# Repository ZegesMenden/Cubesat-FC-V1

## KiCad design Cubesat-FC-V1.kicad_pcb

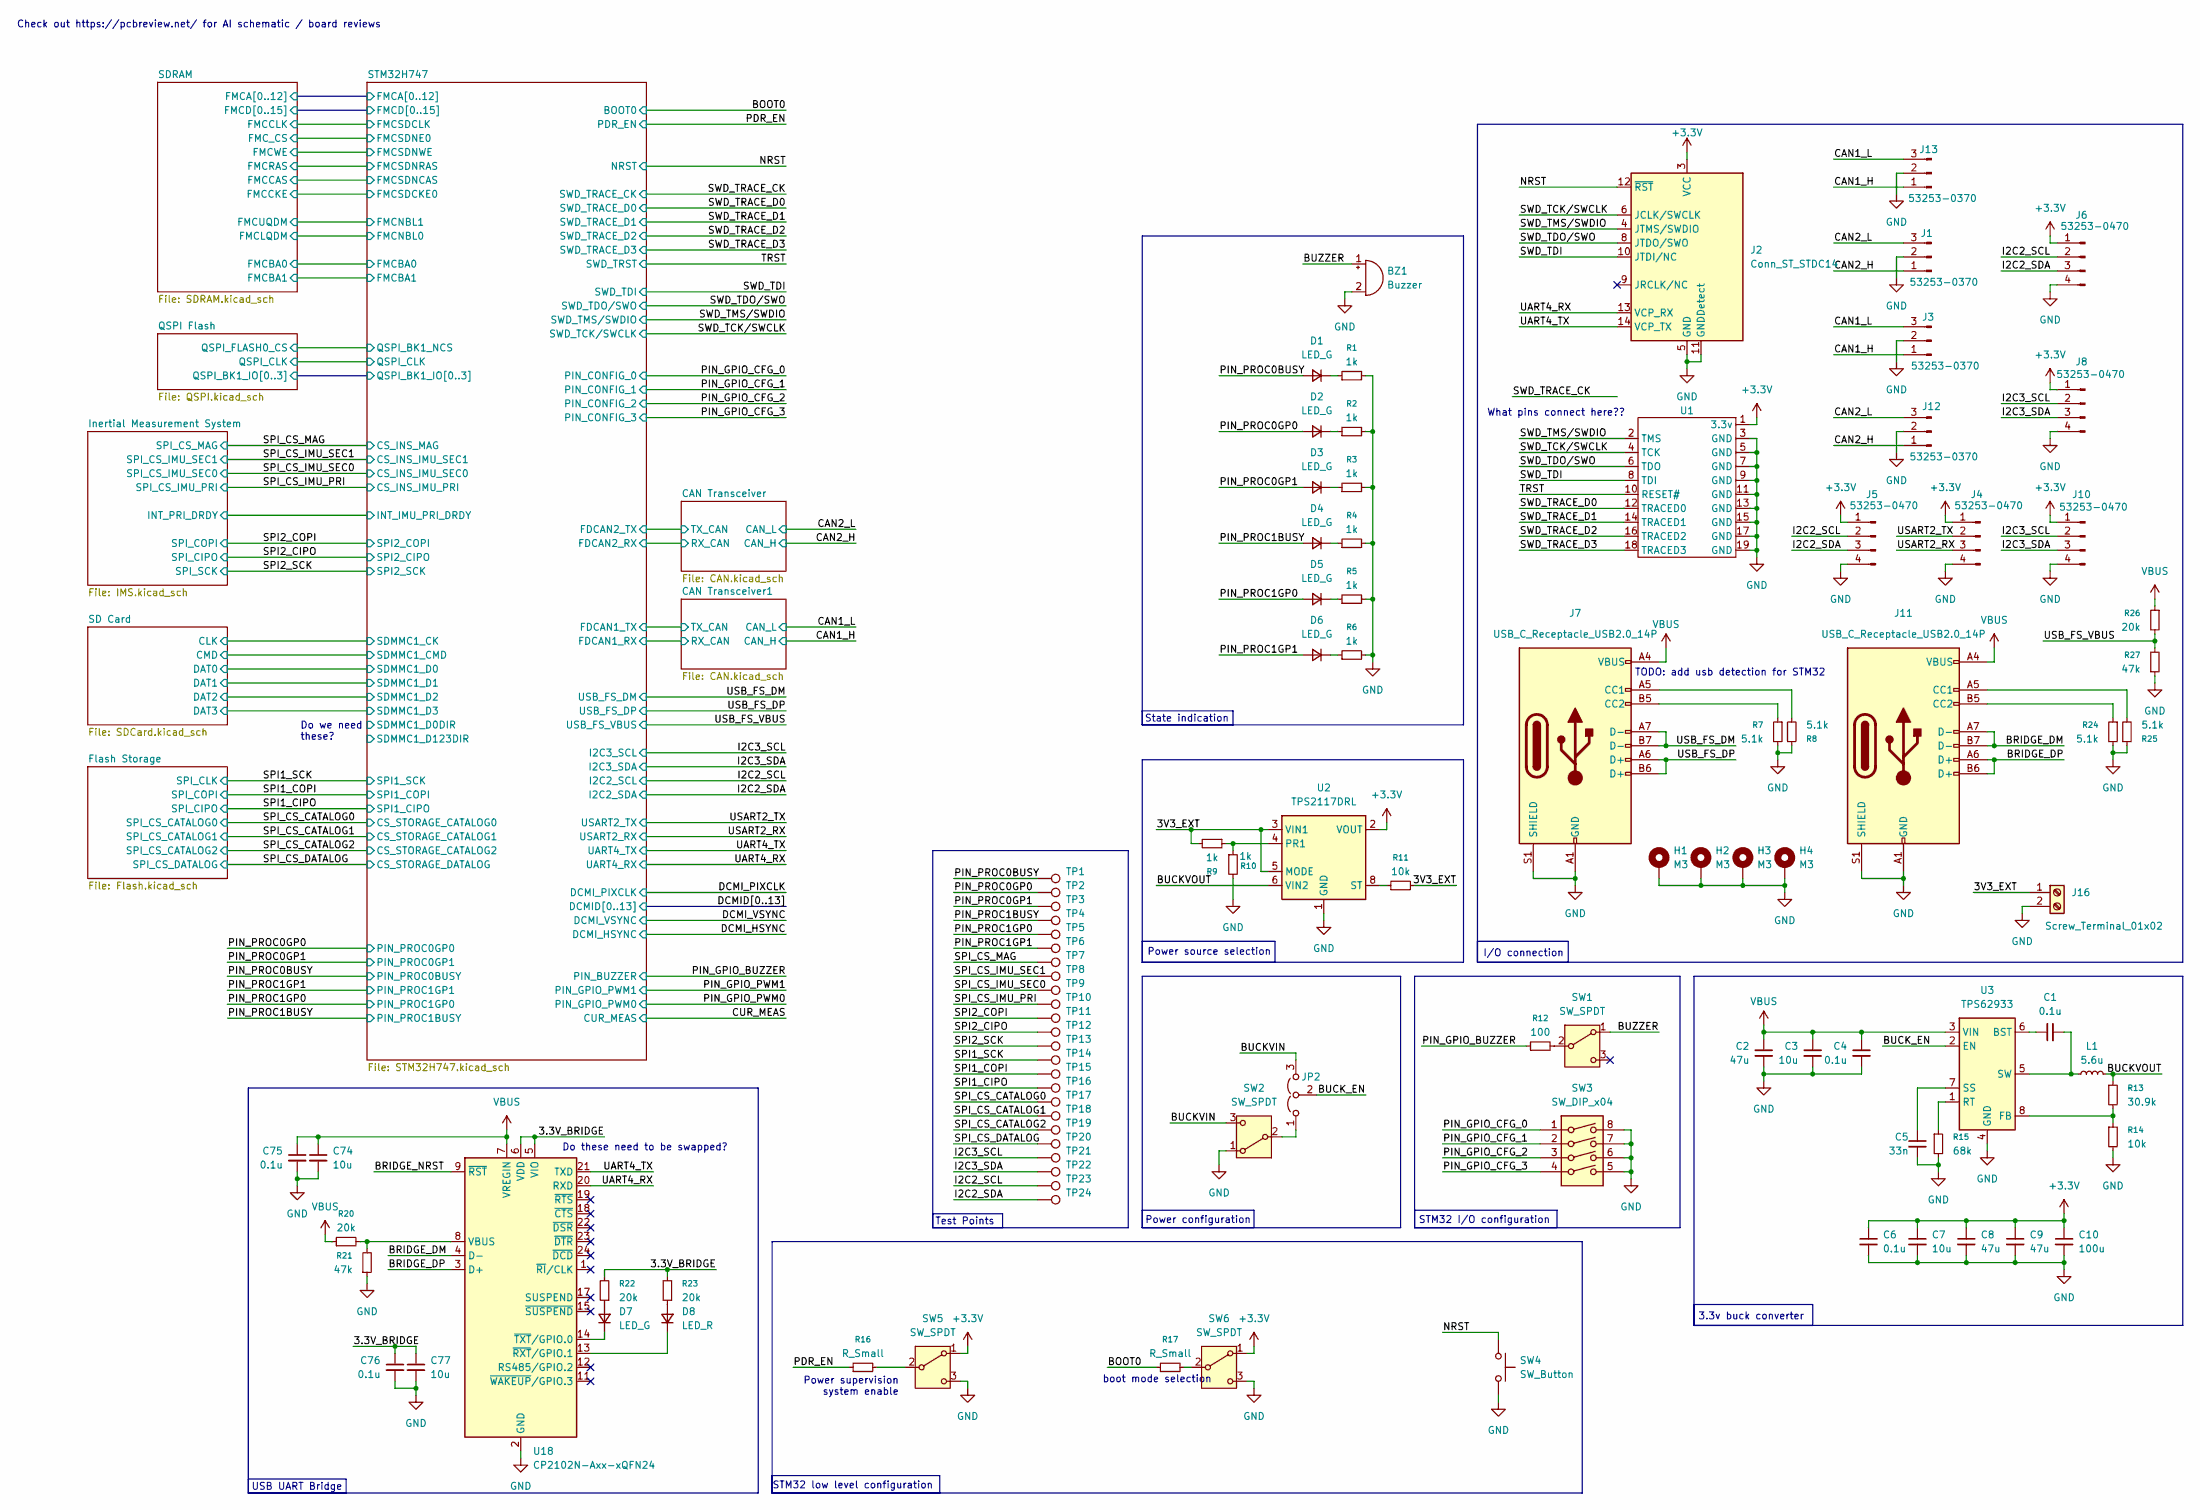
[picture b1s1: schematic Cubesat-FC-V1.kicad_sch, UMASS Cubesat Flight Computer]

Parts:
BZ1: Buzzer; Buzzer_Murata_PKMCS0909E
C1, C75, C76: 0.1u; C_0402_1005Metric; voltage 10
C2, C8, C9: 47u; C_1206_3216Metric; voltage 30
C3, C7: 10u; C_1206_3216Metric; voltage 30
C4, C6: 0.1u; C_1206_3216Metric; voltage 30
C5: 33n; C_0402_1005Metric; voltage 10
C10: 100u; C_1206_3216Metric; voltage 30
C74, C77: 10u; C_0402_1005Metric; voltage 10
D1, D2, D3, D4, D5, D6, D7: LED_G; LED_0603_1608Metric
D8: LED_R; LED_0603_1608Metric
H1, H2, H3, H4: M3; MountingHole_3.2mm_M3_ISO7380_Pad_TopBottom
J1, J3, J12, J13: 53253-0370; Molex_Micro-Latch_53253-0370_1x03_P2.00mm_Vertical
J2: Conn_ST_STDC14; PinHeader_2x07_P2.54mm_Vertical
J4, J5, J6, J8, J10: 53253-0470; Molex_Micro-Latch_53253-0470_1x04_P2.00mm_Vertical
J7, J11: USB_C_Receptacle_USB2.0_14P; USB_C_Receptacle_GCT_USB4105-xx-A_16P_TopMnt_Horizontal
J16: Screw_Terminal_01x02; TerminalBlock_Phoenix_MKDS-1,5-2-5.08_1x02_P5.08mm_Horizont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
JP2: Jumper_3_Open; SolderJumper-3_P1.3mm_Open_RoundedPad1.0x1.5mm
L1: 5.6u; L_Coilcraft_XAL7070-XXX
R1, R2, R3, R4, R5, R6, R9, R10: 1k; R_0402_1005Metric; voltage 50
R7, R8, R24, R25: 5.1k; R_0402_1005Metric; voltage 50
R11, R14: 10k; R_0402_1005Metric; voltage 50
R12: 100; R_0402_1005Metric; voltage 50
R13: 30.9k; R_0402_1005Metric; voltage 50
R15: 68k; R_0402_1005Metric; voltage 50
R16, R17: R_Small; R_0402_1005Metric; voltage 50
R20, R22, R23, R26: 20k; R_0402_1005Metric; voltage 50
R21, R27: 47k; R_0402_1005Metric; voltage 50
SW1, SW2, SW5, SW6: SW_SPDT; SW_CK_JS202011CQN_DPDT_Straight
SW3: SW_DIP_x04; SW_DIP_SPSTx04_Slide_6.7x11.72mm_W7.62mm_P2.54mm_LowProfile
SW4: SW_Button; SW_SPST_PTS810
TP1, TP2, TP3, TP4, TP5, TP6, TP7, TP8, TP9, TP10, TP11, TP12, TP13, TP14, TP15, TP16, TP17, TP18, TP19, TP20, TP21, TP22, TP23, TP24: TestPoint; TestPoint_Pad_D1.5mm
U1: PinHeader_2x10_P2.54mm_Vertical
U2: TPS2117DRL; SOT-583-8
U3: TPS62933; SOT-583-8
U18: CP2102N-Axx-xQFN24; QFN-24-1EP_4x4mm_P0.5mm_EP2.6x2.6mm

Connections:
+3.3V: C6.1, C7.1, C8.1, C9.1, C10.1, J2.3 (VCC), J4.1, J5.1, J6.1, J8.1, J10.1, SW5.1 (A), SW6.1 (A), U1.1 (3.3v), U2.2 (VOUT), U2.7 (VOUT); also elsewhere on the board
/3.3V_BRIDGE: C76.1, C77.1, R22.2, R23.2, U18.5 (VIO), U18.6 (VDD)
/3V3_EXT: J16.1, R9.2, R11.2, U2.3 (VIN1), U2.5 (MODE)
/BOOT0: R17.1; also elsewhere on the board
/BRIDGE_DM: J11.A7 (D-), J11.B7 (D-), U18.4 (D-)
/BRIDGE_DP: J11.A6 (D+), J11.B6 (D+), U18.3 (D+)
/BRIDGE_NRST: U18.9 (~RST)
/BUCKVIN: JP2.3 (B), SW2.3 (C)
/BUCKVOUT: L1.2, R13.1, U2.6 (VIN2)
/BUCK_EN: JP2.2 (C), U3.2 (EN)
/BUZZER: BZ1.1 (+), SW1.1 (A)
/CAN1_H: J3.1, J13.1; also elsewhere on the board
/CAN1_L: J3.3, J13.3; also elsewhere on the board
/CAN2_H: J1.1, J12.1; also elsewhere on the board
/CAN2_L: J1.3, J12.3; also elsewhere on the board
/I2C2_SCL: J5.2, J6.2, TP23.1; also elsewhere on the board
/I2C2_SDA: J5.3, J6.3, TP24.1; also elsewhere on the board
/I2C3_SCL: J8.2, J10.2, TP21.1; also elsewhere on the board
/I2C3_SDA: J8.3, J10.3, TP22.1; also elsewhere on the board
/NRST: J2.12 (~RST), SW4.1; also elsewhere on the board
/PDR_EN: R16.1; also elsewhere on the board
/PIN_GPIO_BUZZER: R12.1; also elsewhere on the board
/PIN_GPIO_CFG_0: SW3.1; also elsewhere on the board
/PIN_GPIO_CFG_1: SW3.2; also elsewhere on the board
/PIN_GPIO_CFG_2: SW3.3; also elsewhere on the board
/PIN_GPIO_CFG_3: SW3.4; also elsewhere on the board
/PIN_PROC0BUSY: D1.2 (A), TP1.1; also elsewhere on the board
/PIN_PROC0GP0: D2.2 (A), TP2.1; also elsewhere on the board
/PIN_PROC0GP1: D3.2 (A), TP3.1; also elsewhere on the board
/PIN_PROC1BUSY: D4.2 (A), TP4.1; also elsewhere on the board
/PIN_PROC1GP0: D5.2 (A), TP5.1; also elsewhere on the board
/PIN_PROC1GP1: D6.2 (A), TP6.1; also elsewhere on the board
/SPI1_CIPO: TP16.1; also elsewhere on the board
/SPI1_COPI: TP15.1; also elsewhere on the board
/SPI1_SCK: TP14.1; also elsewhere on the board
/SPI2_CIPO: TP12.1; also elsewhere on the board
/SPI2_COPI: TP11.1; also elsewhere on the board
/SPI2_SCK: TP13.1; also elsewhere on the board
/SPI_CS_CATALOG0: TP17.1; also elsewhere on the board
/SPI_CS_CATALOG1: TP18.1; also elsewhere on the board
/SPI_CS_CATALOG2: TP19.1; also elsewhere on the board
/SPI_CS_DATALOG: TP20.1; also elsewhere on the board
/SPI_CS_IMU_PRI: TP10.1; also elsewhere on the board
/SPI_CS_IMU_SEC0: TP9.1; also elsewhere on the board
/SPI_CS_IMU_SEC1: TP8.1; also elsewhere on the board
/SPI_CS_MAG: TP7.1; also elsewhere on the board
/SWD_TCK/SWCLK: J2.6 (JCLK/SWCLK), U1.4 (TCK); also elsewhere on the board
/SWD_TDI: J2.10 (JTDI/NC), U1.8 (TDI); also elsewhere on the board
/SWD_TDO/SWO: J2.8 (JTDO/SWO), U1.6 (TDO); also elsewhere on the board
/SWD_TMS/SWDIO: J2.4 (JTMS/SWDIO), U1.2 (TMS); also elsewhere on the board
/SWD_TRACE_D0: U1.12 (TRACED0); also elsewhere on the board
/SWD_TRACE_D1: U1.14 (TRACED1); also elsewhere on the board
/SWD_TRACE_D2: U1.16 (TRACED2); also elsewhere on the board
/SWD_TRACE_D3: U1.18 (TRACED3); also elsewhere on the board
/TRST: U1.10 (RESET#); also elsewhere on the board
/UART4_RX: J2.13 (VCP_RX), U18.20 (RXD); also elsewhere on the board
/UART4_TX: J2.14 (VCP_TX), U18.21 (TXD); also elsewhere on the board
/USART2_RX: J4.3; also elsewhere on the board
/USART2_TX: J4.2; also elsewhere on the board
/USB_FS_DM: J7.A7 (D-), J7.B7 (D-); also elsewhere on the board
/USB_FS_DP: J7.A6 (D+), J7.B6 (D+); also elsewhere on the board
/USB_FS_VBUS: R26.2, R27.2; also elsewhere on the board
GND: BZ1.2 (-), C2.2, C3.2, C4.2, C5.2, C6.2, C7.2, C8.2, C9.2, C10.2, C74.2, C75.2, C76.2, C77.2, H1.1, H2.1, H3.1, H4.1, J1.2, J2.5 (GND), J2.7 (GND), J2.11 (GNDDetect), J3.2, J4.4, J5.4, J6.4, J7.A1 (GND), J7.A12 (GND), J7.B1 (GND), J7.B12 (GND), J7.S1 (SHIELD), J8.4, J10.4, J11.A1 (GND), J11.A12 (GND), J11.B1 (GND), J11.B12 (GND), J11.S1 (SHIELD), J12.2, J13.2, J16.2, R1.2, R2.2, R3.2, R4.2, R5.2, R6.2, R7.2, R8.1, R10.2, R14.2, R15.2, R21.1, R24.2, R25.1, R27.1, SW2.1 (A), SW3.5, SW3.6, SW3.7, SW3.8, SW4.2, SW5.3 (C), SW6.3 (C), U1.3 (GND), U1.5 (GND), U1.7 (GND), U1.9 (GND), U1.11 (GND), U1.13 (GND), U1.15 (GND), U1.17 (GND), U1.19 (GND), U2.1 (GND), U3.4 (GND), U18.2 (GND), U18.25 (GND); also elsewhere on the board
unnamed: D1.1 (K), R1.1
unnamed: D2.1 (K), R2.1
unnamed: D3.1 (K), R3.1
unnamed: D4.1 (K), R4.1
unnamed: D5.1 (K), R5.1
unnamed: D6.1 (K), R6.1
unnamed: D7.2 (A), R22.1
unnamed: D7.1 (K), U18.14 (~TXT/GPIO.0)
unnamed: D8.2 (A), R23.1
unnamed: D8.1 (K), U18.13 (~RXT/GPIO.1)
unnamed: J7.A5 (CC1), R8.2
unnamed: J7.B5 (CC2), R7.1
unnamed: J11.A5 (CC1), R25.2
unnamed: J11.B5 (CC2), R24.1
unnamed: JP2.1 (A), SW2.2 (B)
unnamed: R12.2, SW1.2 (B)
unnamed: R16.2, SW5.2 (B)
unnamed: R17.2, SW6.2 (B)
unnamed: R9.1, R10.1, U2.4 (PR1)
unnamed: R11.1, U2.8 (ST)
unnamed: C1.1, U3.6 (BST)
unnamed: R13.2, R14.1, U3.8 (FB)
unnamed: R15.1, U3.1 (RT)
unnamed: C5.1, U3.7 (SS)
unnamed: C1.2, L1.1, U3.5 (SW)
unnamed: R20.2, R21.2, U18.8 (VBUS)
VBUS: C2.1, C3.1, C4.1, C74.1, C75.1, J7.A4 (VBUS), J7.A9 (VBUS), J7.B4 (VBUS), J7.B9 (VBUS), J11.A4 (VBUS), J11.A9 (VBUS), J11.B4 (VBUS), J11.B9 (VBUS), R20.1, R26.1, U3.3 (VIN), U18.7 (VREGIN)

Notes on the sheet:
Test Points
Power configuration
Do these need to be swapped?
I/O connection
Power source selection
TODO: add usb detection for STM32
Do we need these?
boot mode selection
Check out https://pcbreview.net/ for AI schematic / board reviews
USB UART Bridge
3.3v buck converter
STM32 low level configuration
What pins connect here??
STM32 I/O configuration
State indication
Power supervision system enable

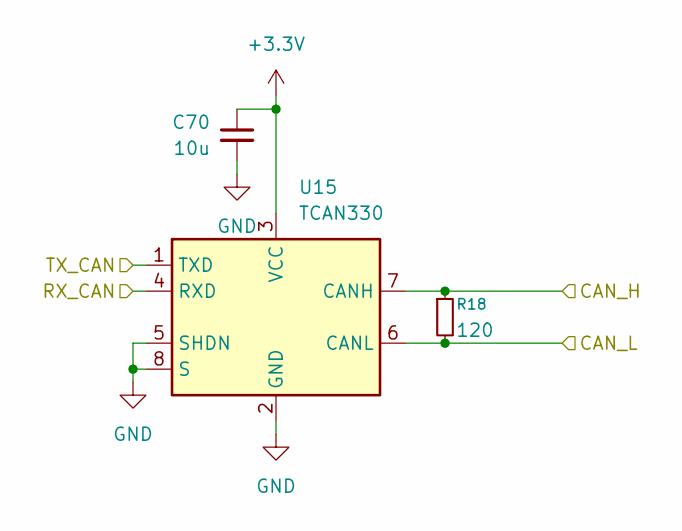
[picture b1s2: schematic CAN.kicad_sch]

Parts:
C70: 10u; C_0402_1005Metric; voltage 5
R18: 120; R_0402_1005Metric; voltage 5
U15: TCAN330; SOT-23-8

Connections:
+3.3V: C70.1, U15.3 (VCC); also elsewhere on the board
/CAN2_H: R18.1, U15.7 (CANH); also elsewhere on the board
/CAN2_L: R18.2, U15.6 (CANL); also elsewhere on the board
/CAN Transceiver/RX_CAN: U15.4 (RXD); also elsewhere on the board
/CAN Transceiver/TX_CAN: U15.1 (TXD); also elsewhere on the board
GND: C70.2, U15.2 (GND), U15.5 (SHDN), U15.8 (S); also elsewhere on the board

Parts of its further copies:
C72: 10u; C_0402_1005Metric; voltage 5
R19: 120; R_0402_1005Metric; voltage 5
U16: TCAN330; SOT-23-8

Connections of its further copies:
+3.3V: C72.1, U16.3 (VCC); also elsewhere on the board
/CAN1_H: R19.1, U16.7 (CANH); also elsewhere on the board
/CAN1_L: R19.2, U16.6 (CANL); also elsewhere on the board
/CAN Transceiver1/RX_CAN: U16.4 (RXD); also elsewhere on the board
/CAN Transceiver1/TX_CAN: U16.1 (TXD); also elsewhere on the board
GND: C72.2, U16.2 (GND), U16.5 (SHDN), U16.8 (S); also elsewhere on the board

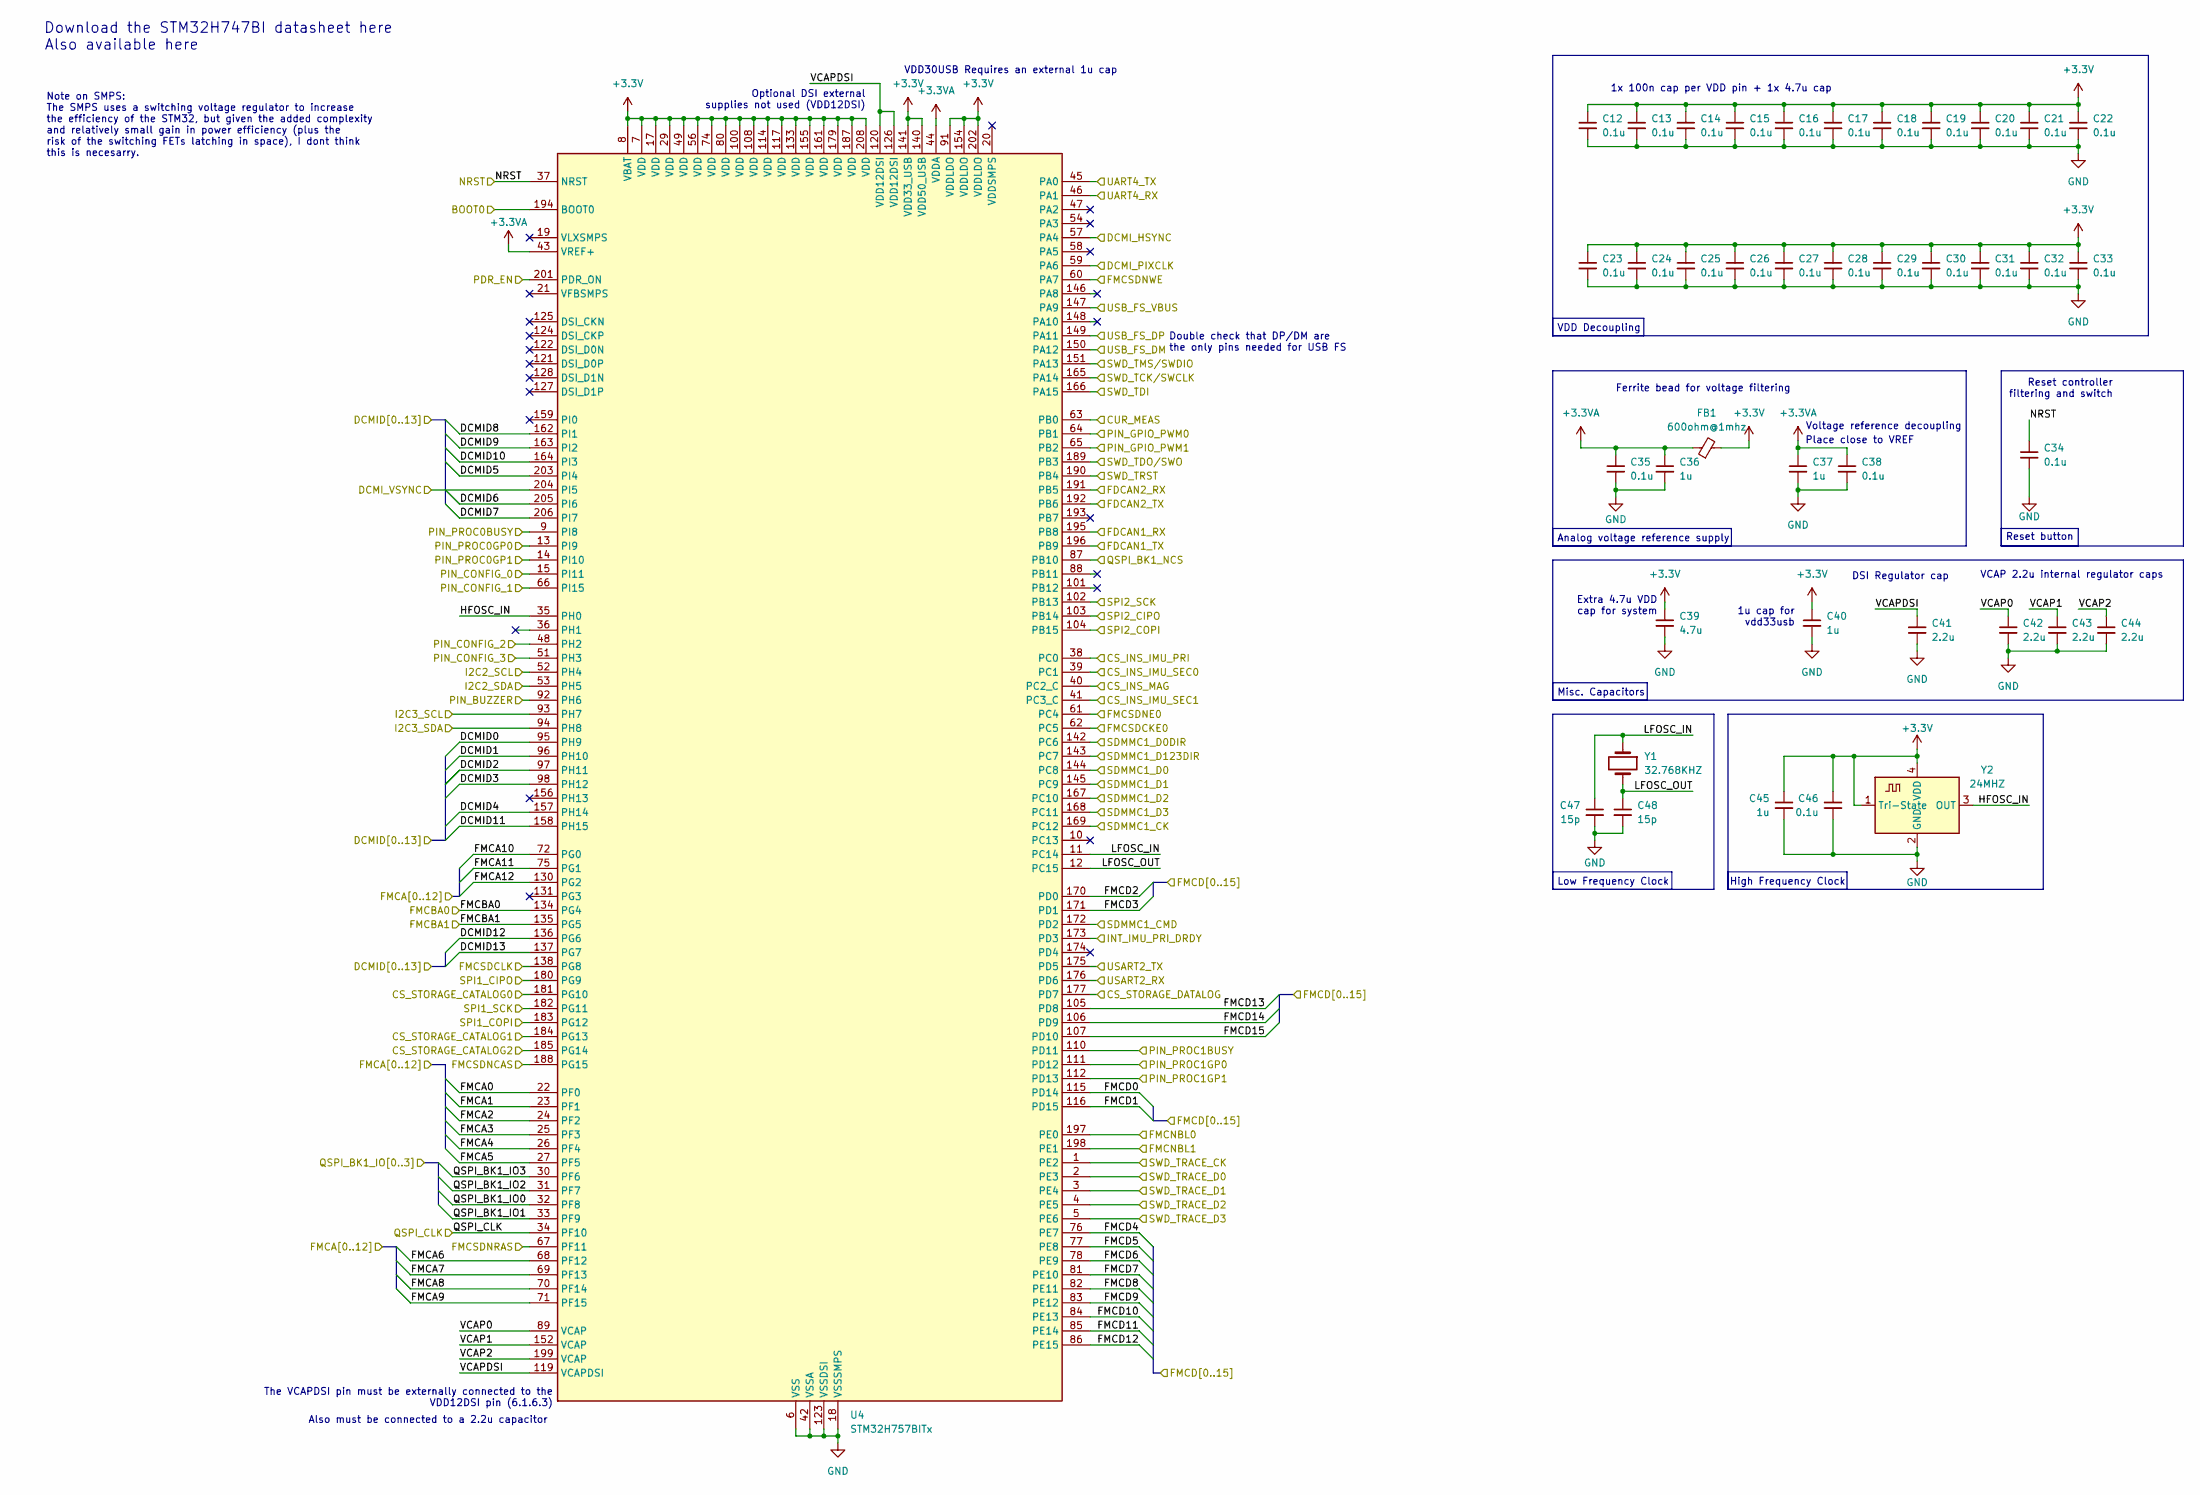
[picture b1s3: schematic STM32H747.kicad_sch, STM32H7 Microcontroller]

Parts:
C12, C13, C14, C15, C16, C17, C18, C19, C20, C21, C22, C23, C24, C25, C26, C27, C28, C29, C30, C31, C32, C33, C34, C35, C38, C46: 0.1u; C_0402_1005Metric; voltage 10
C36, C37, C40, C45: 1u; C_0402_1005Metric; voltage 10
C39: 4.7u; C_0402_1005Metric; voltage 10
C41, C42, C43, C44: 2.2u; C_0402_1005Metric; voltage 10
C47, C48: 15p; C_0402_1005Metric; voltage 10
FB1: 600ohm@1mhz; R_0402_1005Metric
U4: STM32H757BITx; LQFP-208_28x28mm_P0.5mm
Y1: 32.768KHZ; Crystal_SMD_Abracon_ABM3-2Pin_5.0x3.2mm
Y2: 24MHZ; Oscillator_SMD_Abracon_ASCO-4Pin_1.6x1.2mm

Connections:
+3.3V: C12.1, C13.1, C14.1, C15.1, C16.1, C17.1, C18.1, C19.1, C20.1, C21.1, C22.1, C23.1, C24.1, C25.1, C26.1, C27.1, C28.1, C29.1, C30.1, C31.1, C32.1, C33.1, C39.1, C40.1, C45.1, C46.1, FB1.2, U4.7 (VDD), U4.8 (VBAT), U4.17 (VDD), U4.29 (VDD), U4.49 (VDD), U4.56 (VDD), U4.74 (VDD), U4.80 (VDD), U4.91 (VDDLDO), U4.100 (VDD), U4.108 (VDD), U4.114 (VDD), U4.117 (VDD), U4.133 (VDD), U4.140 (VDD50_USB), U4.141 (VDD33_USB), U4.154 (VDDLDO), U4.155 (VDD), U4.161 (VDD), U4.179 (VDD), U4.187 (VDD), U4.202 (VDDLDO), U4.208 (VDD), Y2.1 (Tri-State), Y2.4 (VDD); also elsewhere on the board
+3.3VA: C35.1, C36.1, C37.1, C38.1, FB1.1, U4.43 (VREF+), U4.44 (VDDA)
/BOOT0: U4.194 (BOOT0); also elsewhere on the board
/CAN Transceiver1/RX_CAN: U4.195 (PB8); also elsewhere on the board
/CAN Transceiver1/TX_CAN: U4.196 (PB9); also elsewhere on the board
/CAN Transceiver/RX_CAN: U4.191 (PB5); also elsewhere on the board
/CAN Transceiver/TX_CAN: U4.192 (PB6); also elsewhere on the board
/CUR_MEAS: U4.63 (PB0)
/DCMID0: U4.95 (PH9)
/DCMID1: U4.96 (PH10)
/DCMID2: U4.97 (PH11)
/DCMID3: U4.98 (PH12)
/DCMID4: U4.157 (PH14)
/DCMID5: U4.203 (PI4)
/DCMID6: U4.205 (PI6)
/DCMID7: U4.206 (PI7)
/DCMID8: U4.162 (PI1)
/DCMID9: U4.163 (PI2)
/DCMID10: U4.164 (PI3)
/DCMID11: U4.158 (PH15)
/DCMID12: U4.136 (PG6)
/DCMID13: U4.137 (PG7)
/DCMI_HSYNC: U4.57 (PA4)
/DCMI_PIXCLK: U4.59 (PA6)
/DCMI_VSYNC: U4.204 (PI5)
/I2C2_SCL: U4.52 (PH4); also elsewhere on the board
/I2C2_SDA: U4.53 (PH5); also elsewhere on the board
/I2C3_SCL: U4.93 (PH7); also elsewhere on the board
/I2C3_SDA: U4.94 (PH8); also elsewhere on the board
/Inertial Measurement System/INT_PRI_DRDY: U4.173 (PD3); also elsewhere on the board
/NRST: C34.1, U4.37 (NRST); also elsewhere on the board
/PDR_EN: U4.201 (PDR_ON); also elsewhere on the board
/PIN_GPIO_BUZZER: U4.92 (PH6); also elsewhere on the board
/PIN_GPIO_CFG_0: U4.15 (PI11); also elsewhere on the board
/PIN_GPIO_CFG_1: U4.66 (PI15); also elsewhere on the board
/PIN_GPIO_CFG_2: U4.48 (PH2); also elsewhere on the board
/PIN_GPIO_CFG_3: U4.51 (PH3); also elsewhere on the board
/PIN_GPIO_PWM0: U4.64 (PB1)
/PIN_GPIO_PWM1: U4.65 (PB2)
/PIN_PROC0BUSY: U4.9 (PI8); also elsewhere on the board
/PIN_PROC0GP0: U4.13 (PI9); also elsewhere on the board
/PIN_PROC0GP1: U4.14 (PI10); also elsewhere on the board
/PIN_PROC1BUSY: U4.110 (PD11); also elsewhere on the board
/PIN_PROC1GP0: U4.111 (PD12); also elsewhere on the board
/PIN_PROC1GP1: U4.112 (PD13); also elsewhere on the board
/QSPI Flash/QSPI_D0: U4.32 (PF8); also elsewhere on the board
/QSPI Flash/QSPI_D1: U4.33 (PF9); also elsewhere on the board
/QSPI Flash/QSPI_D2: U4.31 (PF7); also elsewhere on the board
/QSPI Flash/QSPI_D3: U4.30 (PF6); also elsewhere on the board
/QSPI Flash/QSPI_FLASH0_CS: U4.87 (PB10); also elsewhere on the board
/SD Card/CLK: U4.169 (PC12); also elsewhere on the board
/SD Card/CMD: U4.172 (PD2); also elsewhere on the board
/SD Card/DAT0: U4.144 (PC8); also elsewhere on the board
/SD Card/DAT1: U4.145 (PC9); also elsewhere on the board
/SD Card/DAT2: U4.167 (PC10); also elsewhere on the board
/SD Card/DAT3: U4.168 (PC11); also elsewhere on the board
/SDRAM/FMCA0: U4.22 (PF0); also elsewhere on the board
/SDRAM/FMCA1: U4.23 (PF1); also elsewhere on the board
/SDRAM/FMCA2: U4.24 (PF2); also elsewhere on the board
/SDRAM/FMCA3: U4.25 (PF3); also elsewhere on the board
/SDRAM/FMCA4: U4.26 (PF4); also elsewhere on the board
/SDRAM/FMCA5: U4.27 (PF5); also elsewhere on the board
/SDRAM/FMCA6: U4.68 (PF12); also elsewhere on the board
/SDRAM/FMCA7: U4.69 (PF13); also elsewhere on the board
/SDRAM/FMCA8: U4.70 (PF14); also elsewhere on the board
/SDRAM/FMCA9: U4.71 (PF15); also elsewhere on the board
/SDRAM/FMCA10: U4.72 (PG0); also elsewhere on the board
/SDRAM/FMCA11: U4.75 (PG1); also elsewhere on the board
/SDRAM/FMCA12: U4.130 (PG2); also elsewhere on the board
/SDRAM/FMCCAS: U4.188 (PG15); also elsewhere on the board
/SDRAM/FMCCKE: U4.62 (PC5); also elsewhere on the board
/SDRAM/FMCCLK: U4.138 (PG8); also elsewhere on the board
/SDRAM/FMCD0: U4.115 (PD14); also elsewhere on the board
/SDRAM/FMCD1: U4.116 (PD15); also elsewhere on the board
/SDRAM/FMCD2: U4.170 (PD0); also elsewhere on the board
/SDRAM/FMCD3: U4.171 (PD1); also elsewhere on the board
/SDRAM/FMCD4: U4.76 (PE7); also elsewhere on the board
/SDRAM/FMCD5: U4.77 (PE8); also elsewhere on the board
/SDRAM/FMCD6: U4.78 (PE9); also elsewhere on the board
/SDRAM/FMCD7: U4.81 (PE10); also elsewhere on the board
/SDRAM/FMCD8: U4.82 (PE11); also elsewhere on the board
/SDRAM/FMCD9: U4.83 (PE12); also elsewhere on the board
/SDRAM/FMCD10: U4.84 (PE13); also elsewhere on the board
/SDRAM/FMCD11: U4.85 (PE14); also elsewhere on the board
/SDRAM/FMCD12: U4.86 (PE15); also elsewhere on the board
/SDRAM/FMCD13: U4.105 (PD8); also elsewhere on the board
/SDRAM/FMCD14: U4.106 (PD9); also elsewhere on the board
/SDRAM/FMCD15: U4.107 (PD10); also elsewhere on the board
/SDRAM/FMCLQDM: U4.197 (PE0); also elsewhere on the board
/SDRAM/FMCRAS: U4.67 (PF11); also elsewhere on the board
/SDRAM/FMCUQDM: U4.198 (PE1); also elsewhere on the board
/SDRAM/FMCWE: U4.60 (PA7); also elsewhere on the board
/SDRAM/FMC_CS: U4.61 (PC4); also elsewhere on the board
/SPI1_CIPO: U4.180 (PG9); also elsewhere on the board
/SPI1_COPI: U4.183 (PG12); also elsewhere on the board
/SPI1_SCK: U4.182 (PG11); also elsewhere on the board
/SPI2_CIPO: U4.103 (PB14); also elsewhere on the board
/SPI2_COPI: U4.104 (PB15); also elsewhere on the board
/SPI2_SCK: U4.102 (PB13); also elsewhere on the board
/SPI_CS_CATALOG0: U4.181 (PG10); also elsewhere on the board
/SPI_CS_CATALOG1: U4.184 (PG13); also elsewhere on the board
/SPI_CS_CATALOG2: U4.185 (PG14); also elsewhere on the board
/SPI_CS_DATALOG: U4.177 (PD7); also elsewhere on the board
/SPI_CS_IMU_PRI: U4.38 (PC0); also elsewhere on the board
/SPI_CS_IMU_SEC0: U4.39 (PC1); also elsewhere on the board
/SPI_CS_IMU_SEC1: U4.41 (PC3_C); also elsewhere on the board
/SPI_CS_MAG: U4.40 (PC2_C); also elsewhere on the board
/STM32H747/FMCBA0: U4.134 (PG4); also elsewhere on the board
/STM32H747/FMCBA1: U4.135 (PG5); also elsewhere on the board
/STM32H747/HFOSC_IN: U4.35 (PH0), Y2.3 (OUT)
/STM32H747/LFOSC_IN: C47.1, U4.11 (PC14), Y1.1
/STM32H747/LFOSC_OUT: C48.1, U4.12 (PC15), Y1.2
/STM32H747/QSPI_CLK: U4.34 (PF10); also elsewhere on the board
/STM32H747/SDMMC1_D0DIR: U4.142 (PC6)
/STM32H747/SDMMC1_D123DIR: U4.143 (PC7)
/STM32H747/VCAP0: C42.1, U4.89 (VCAP)
/STM32H747/VCAP1: C43.1, U4.152 (VCAP)
/STM32H747/VCAP2: C44.1, U4.199 (VCAP)
/STM32H747/VCAPDSI: C41.1, U4.119 (VCAPDSI), U4.120 (VDD12DSI), U4.126 (VDD12DSI)
/SWD_TCK/SWCLK: U4.165 (PA14); also elsewhere on the board
/SWD_TDI: U4.166 (PA15); also elsewhere on the board
/SWD_TDO/SWO: U4.189 (PB3); also elsewhere on the board
/SWD_TMS/SWDIO: U4.151 (PA13); also elsewhere on the board
/SWD_TRACE_CK: U4.1 (PE2)
/SWD_TRACE_D0: U4.2 (PE3); also elsewhere on the board
/SWD_TRACE_D1: U4.3 (PE4); also elsewhere on the board
/SWD_TRACE_D2: U4.4 (PE5); also elsewhere on the board
/SWD_TRACE_D3: U4.5 (PE6); also elsewhere on the board
/TRST: U4.190 (PB4); also elsewhere on the board
/UART4_RX: U4.46 (PA1); also elsewhere on the board
/UART4_TX: U4.45 (PA0); also elsewhere on the board
/USART2_RX: U4.176 (PD6); also elsewhere on the board
/USART2_TX: U4.175 (PD5); also elsewhere on the board
/USB_FS_DM: U4.150 (PA12); also elsewhere on the board
/USB_FS_DP: U4.149 (PA11); also elsewhere on the board
/USB_FS_VBUS: U4.147 (PA9); also elsewhere on the board
GND: C12.2, C13.2, C14.2, C15.2, C16.2, C17.2, C18.2, C19.2, C20.2, C21.2, C22.2, C23.2, C24.2, C25.2, C26.2, C27.2, C28.2, C29.2, C30.2, C31.2, C32.2, C33.2, C34.2, C35.2, C36.2, C37.2, C38.2, C39.2, C40.2, C41.2, C42.2, C43.2, C44.2, C45.2, C46.2, C47.2, C48.2, U4.6 (VSS), U4.16 (VSS), U4.18 (VSSSMPS), U4.28 (VSS), U4.42 (VSSA), U4.50 (VSS), U4.55 (VSS), U4.73 (VSS), U4.79 (VSS), U4.90 (VSS), U4.99 (VSS), U4.109 (VSS), U4.113 (VSS), U4.118 (VSS), U4.123 (VSSDSI), U4.129 (VSSDSI), U4.132 (VSS), U4.139 (VSS), U4.153 (VSS), U4.160 (VSS), U4.178 (VSS), U4.186 (VSS), U4.200 (VSS), U4.207 (VSS), Y2.2 (GND); also elsewhere on the board

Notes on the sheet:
1u cap for vdd33usb
Reset controller filtering and switch
VDD30USB Requires an external 1u cap
Extra 4.7u VDD cap for system
Double check that DP/DM are the only pins needed for USB FS
Low Frequency Clock
Ferrite bead for voltage filtering
Misc. Capacitors
Also must be connected to a 2.2u capacitor
Voltage reference decoupling
Optional DSI external supplies not used (VDD12DSI)
The VCAPDSI pin must be externally connected to the VDD12DSI pin (6.1.6.3)
VCAP 2.2u internal regulator caps
Reset button
Download the STM32H747BI datasheet here
1x 100n cap per VDD pin + 1x 4.7u cap
Analog voltage reference supply
High Frequency Clock
Place close to VREF
Note on SMPS: The SMPS uses a switching voltage regulator to increase the efficiency of the STM32, but given the added complexity and relatively small gain in power efficiency (plus the risk of the switching FETs latching in space), I dont think this is necesarry.
DSI Regulator cap
VDD Decoupling
Also available here

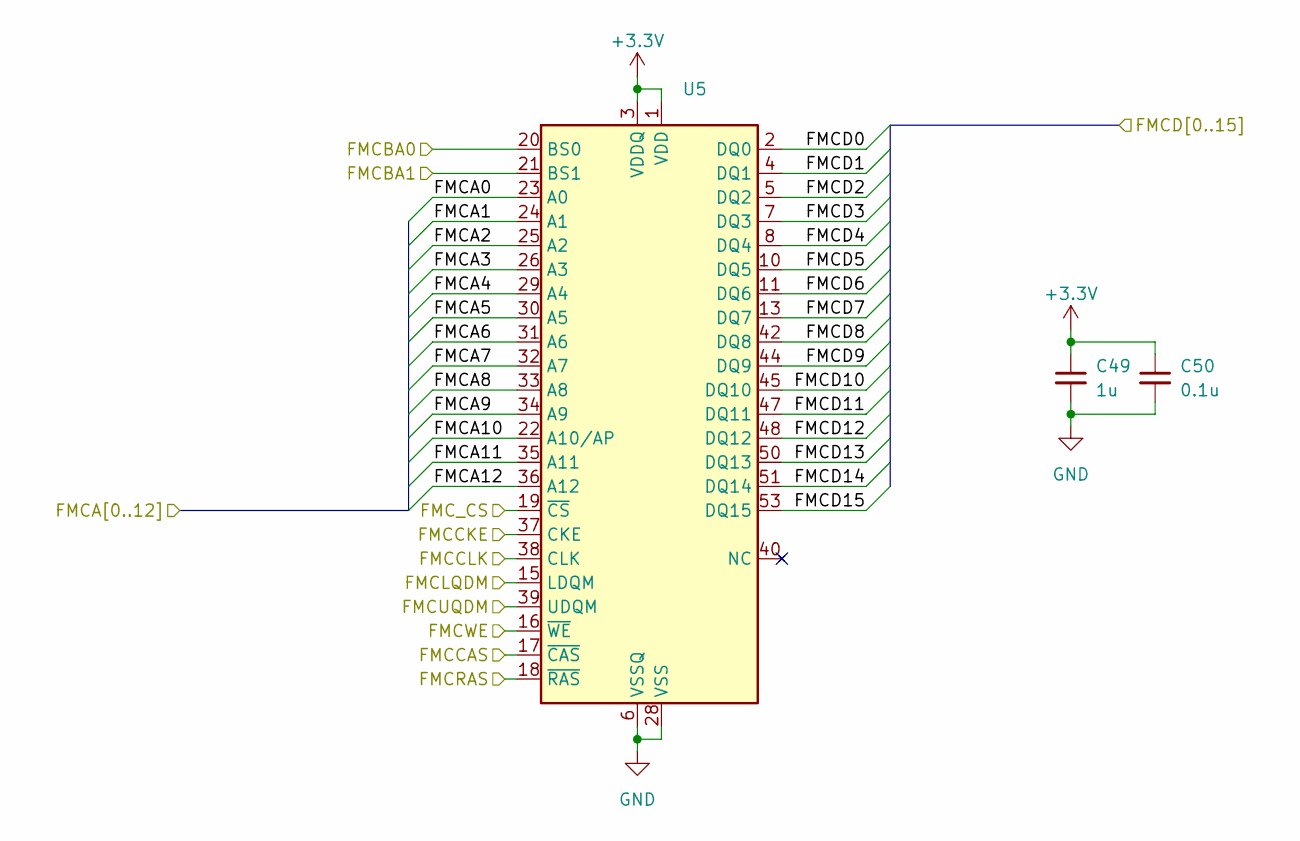
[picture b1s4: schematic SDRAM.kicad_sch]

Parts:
C49: 1u; C_0402_1005Metric; voltage 10
C50: 0.1u; C_0402_1005Metric; voltage 10
U5: TSOP-II-54_22.2x10.16mm_P0.8mm

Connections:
+3.3V: C49.1, C50.1, U5.1 (VDD), U5.3 (VDDQ), U5.9 (VDDQ), U5.14 (VDD), U5.27 (VDD), U5.43 (VDDQ), U5.49 (VDDQ); also elsewhere on the board
/SDRAM/FMCA0: U5.23 (A0); also elsewhere on the board
/SDRAM/FMCA1: U5.24 (A1); also elsewhere on the board
/SDRAM/FMCA2: U5.25 (A2); also elsewhere on the board
/SDRAM/FMCA3: U5.26 (A3); also elsewhere on the board
/SDRAM/FMCA4: U5.29 (A4); also elsewhere on the board
/SDRAM/FMCA5: U5.30 (A5); also elsewhere on the board
/SDRAM/FMCA6: U5.31 (A6); also elsewhere on the board
/SDRAM/FMCA7: U5.32 (A7); also elsewhere on the board
/SDRAM/FMCA8: U5.33 (A8); also elsewhere on the board
/SDRAM/FMCA9: U5.34 (A9); also elsewhere on the board
/SDRAM/FMCA10: U5.22 (A10/AP); also elsewhere on the board
/SDRAM/FMCA11: U5.35 (A11); also elsewhere on the board
/SDRAM/FMCA12: U5.36 (A12); also elsewhere on the board
/SDRAM/FMCCAS: U5.17 (~CAS); also elsewhere on the board
/SDRAM/FMCCKE: U5.37 (CKE); also elsewhere on the board
/SDRAM/FMCCLK: U5.38 (CLK); also elsewhere on the board
/SDRAM/FMCD0: U5.2 (DQ0); also elsewhere on the board
/SDRAM/FMCD1: U5.4 (DQ1); also elsewhere on the board
/SDRAM/FMCD2: U5.5 (DQ2); also elsewhere on the board
/SDRAM/FMCD3: U5.7 (DQ3); also elsewhere on the board
/SDRAM/FMCD4: U5.8 (DQ4); also elsewhere on the board
/SDRAM/FMCD5: U5.10 (DQ5); also elsewhere on the board
/SDRAM/FMCD6: U5.11 (DQ6); also elsewhere on the board
/SDRAM/FMCD7: U5.13 (DQ7); also elsewhere on the board
/SDRAM/FMCD8: U5.42 (DQ8); also elsewhere on the board
/SDRAM/FMCD9: U5.44 (DQ9); also elsewhere on the board
/SDRAM/FMCD10: U5.45 (DQ10); also elsewhere on the board
/SDRAM/FMCD11: U5.47 (DQ11); also elsewhere on the board
/SDRAM/FMCD12: U5.48 (DQ12); also elsewhere on the board
/SDRAM/FMCD13: U5.50 (DQ13); also elsewhere on the board
/SDRAM/FMCD14: U5.51 (DQ14); also elsewhere on the board
/SDRAM/FMCD15: U5.53 (DQ15); also elsewhere on the board
/SDRAM/FMCLQDM: U5.15 (LDQM); also elsewhere on the board
/SDRAM/FMCRAS: U5.18 (~RAS); also elsewhere on the board
/SDRAM/FMCUQDM: U5.39 (UDQM); also elsewhere on the board
/SDRAM/FMCWE: U5.16 (~WE); also elsewhere on the board
/SDRAM/FMC_CS: U5.19 (~CS); also elsewhere on the board
/STM32H747/FMCBA0: U5.20 (BS0); also elsewhere on the board
/STM32H747/FMCBA1: U5.21 (BS1); also elsewhere on the board
GND: C49.2, C50.2, U5.6 (VSSQ), U5.12 (VSSQ), U5.28 (VSS), U5.41 (VSS), U5.46 (VSSQ), U5.52 (VSSQ), U5.54 (VSS); also elsewhere on the board

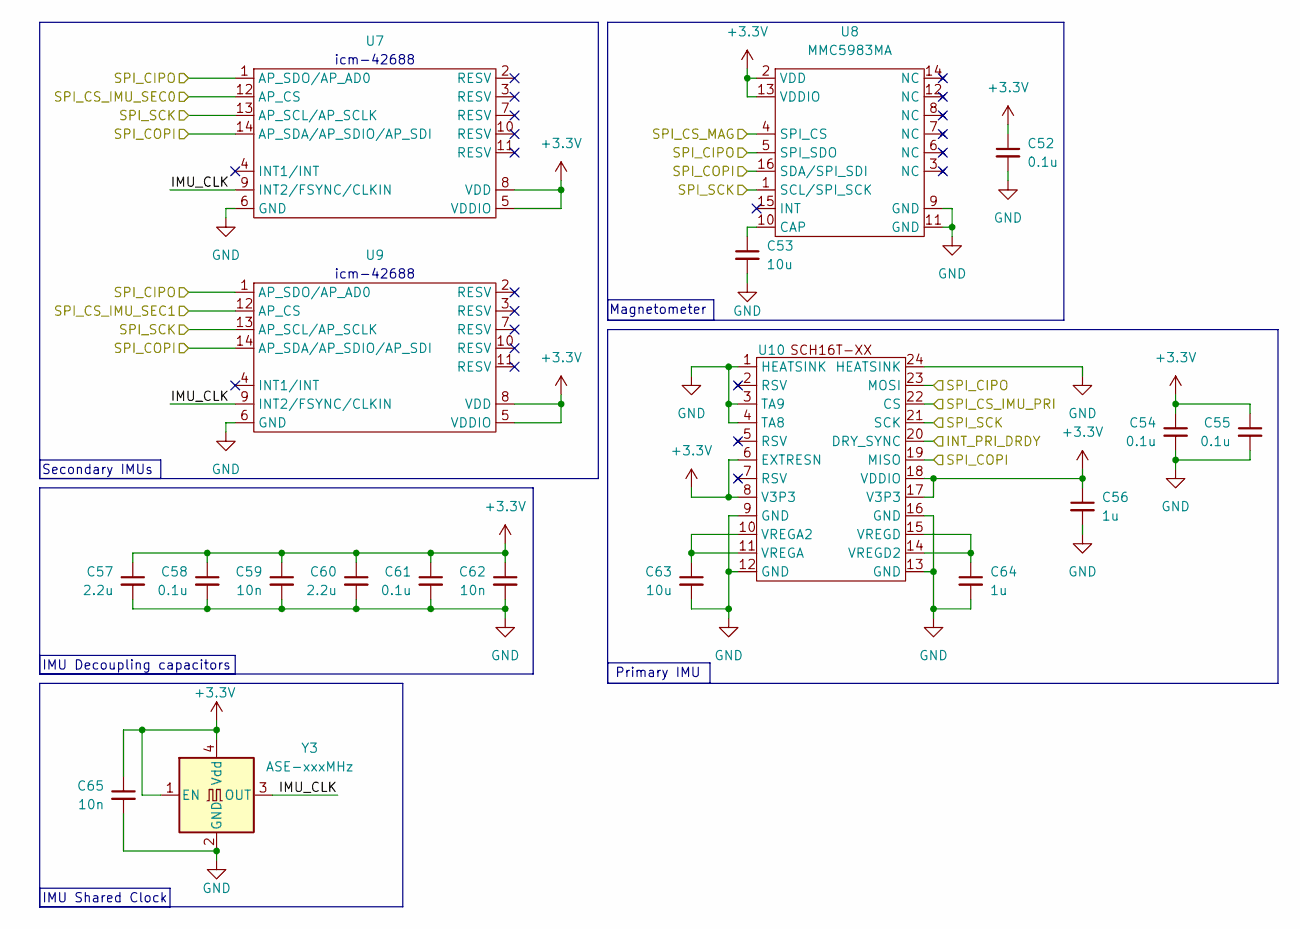
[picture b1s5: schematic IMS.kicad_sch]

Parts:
C52, C54, C55, C58, C61: 0.1u; C_0402_1005Metric; voltage 10
C53, C63: 10u; C_0402_1005Metric; voltage 10
C56, C64: 1u; C_0402_1005Metric; voltage 10
C57, C60: 2.2u; C_0402_1005Metric; voltage 10
C59, C62, C65: 10n; C_0402_1005Metric; voltage 10
U7, U9: LGA-14_3x2.5mm_P0.5mm_LayoutBorder3x4y
U8: MMC5983MA; LGA-16_3x3mm_P0.5mm
U10: SCH16T
Y3: ASE-xxxMHz; Oscillator_SMD_Abracon_ASE-4Pin_3.2x2.5mm

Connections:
+3.3V: C52.1, C54.1, C55.1, C56.1, C57.1, C58.1, C59.1, C60.1, C61.1, C62.1, C65.1, U7.5 (VDDIO), U7.8 (VDD), U8.2 (VDD), U8.13 (VDDIO), U9.5 (VDDIO), U9.8 (VDD), U10.6 (EXTRESN), U10.8 (V3P3), U10.17 (V3P3), U10.18 (VDDIO), Y3.1 (EN), Y3.4 (Vdd); also elsewhere on the board
/Inertial Measurement System/IMU_CLK: U7.9 (INT2/FSYNC/CLKIN), U9.9 (INT2/FSYNC/CLKIN), Y3.3 (OUT)
/Inertial Measurement System/INT_PRI_DRDY: U10.20 (DRY_SYNC); also elsewhere on the board
/SPI2_CIPO: U7.1 (AP_SDO/AP_AD0), U8.5 (SPI_SDO), U9.1 (AP_SDO/AP_AD0), U10.23 (MOSI); also elsewhere on the board
/SPI2_COPI: U7.14 (AP_SDA/AP_SDIO/AP_SDI), U8.16 (SDA/SPI_SDI), U9.14 (AP_SDA/AP_SDIO/AP_SDI), U10.19 (MISO); also elsewhere on the board
/SPI2_SCK: U7.13 (AP_SCL/AP_SCLK), U8.1 (SCL/SPI_SCK), U9.13 (AP_SCL/AP_SCLK), U10.21 (SCK); also elsewhere on the board
/SPI_CS_IMU_PRI: U10.22 (CS); also elsewhere on the board
/SPI_CS_IMU_SEC0: U7.12 (AP_CS); also elsewhere on the board
/SPI_CS_IMU_SEC1: U9.12 (AP_CS); also elsewhere on the board
/SPI_CS_MAG: U8.4 (SPI_CS); also elsewhere on the board
GND: C52.2, C53.2, C54.2, C55.2, C56.2, C57.2, C58.2, C59.2, C60.2, C61.2, C62.2, C63.2, C64.2, C65.2, U7.6 (GND), U8.9 (GND), U8.11 (GND), U9.6 (GND), U10.1 (HEATSINK), U10.3 (TA9), U10.4 (TA8), U10.9 (GND), U10.12 (GND), U10.13 (GND), U10.16 (GND), U10.24 (HEATSINK), Y3.2 (GND); also elsewhere on the board
unnamed: C53.1, U8.10 (CAP)
unnamed: C63.1, U10.10 (VREGA2), U10.11 (VREGA)
unnamed: C64.1, U10.14 (VREGD2), U10.15 (VREGD)

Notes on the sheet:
Primary IMU
icm-42688
Magnetometer
IMU Decoupling capacitors
Secondary IMUs
IMU Shared Clock
